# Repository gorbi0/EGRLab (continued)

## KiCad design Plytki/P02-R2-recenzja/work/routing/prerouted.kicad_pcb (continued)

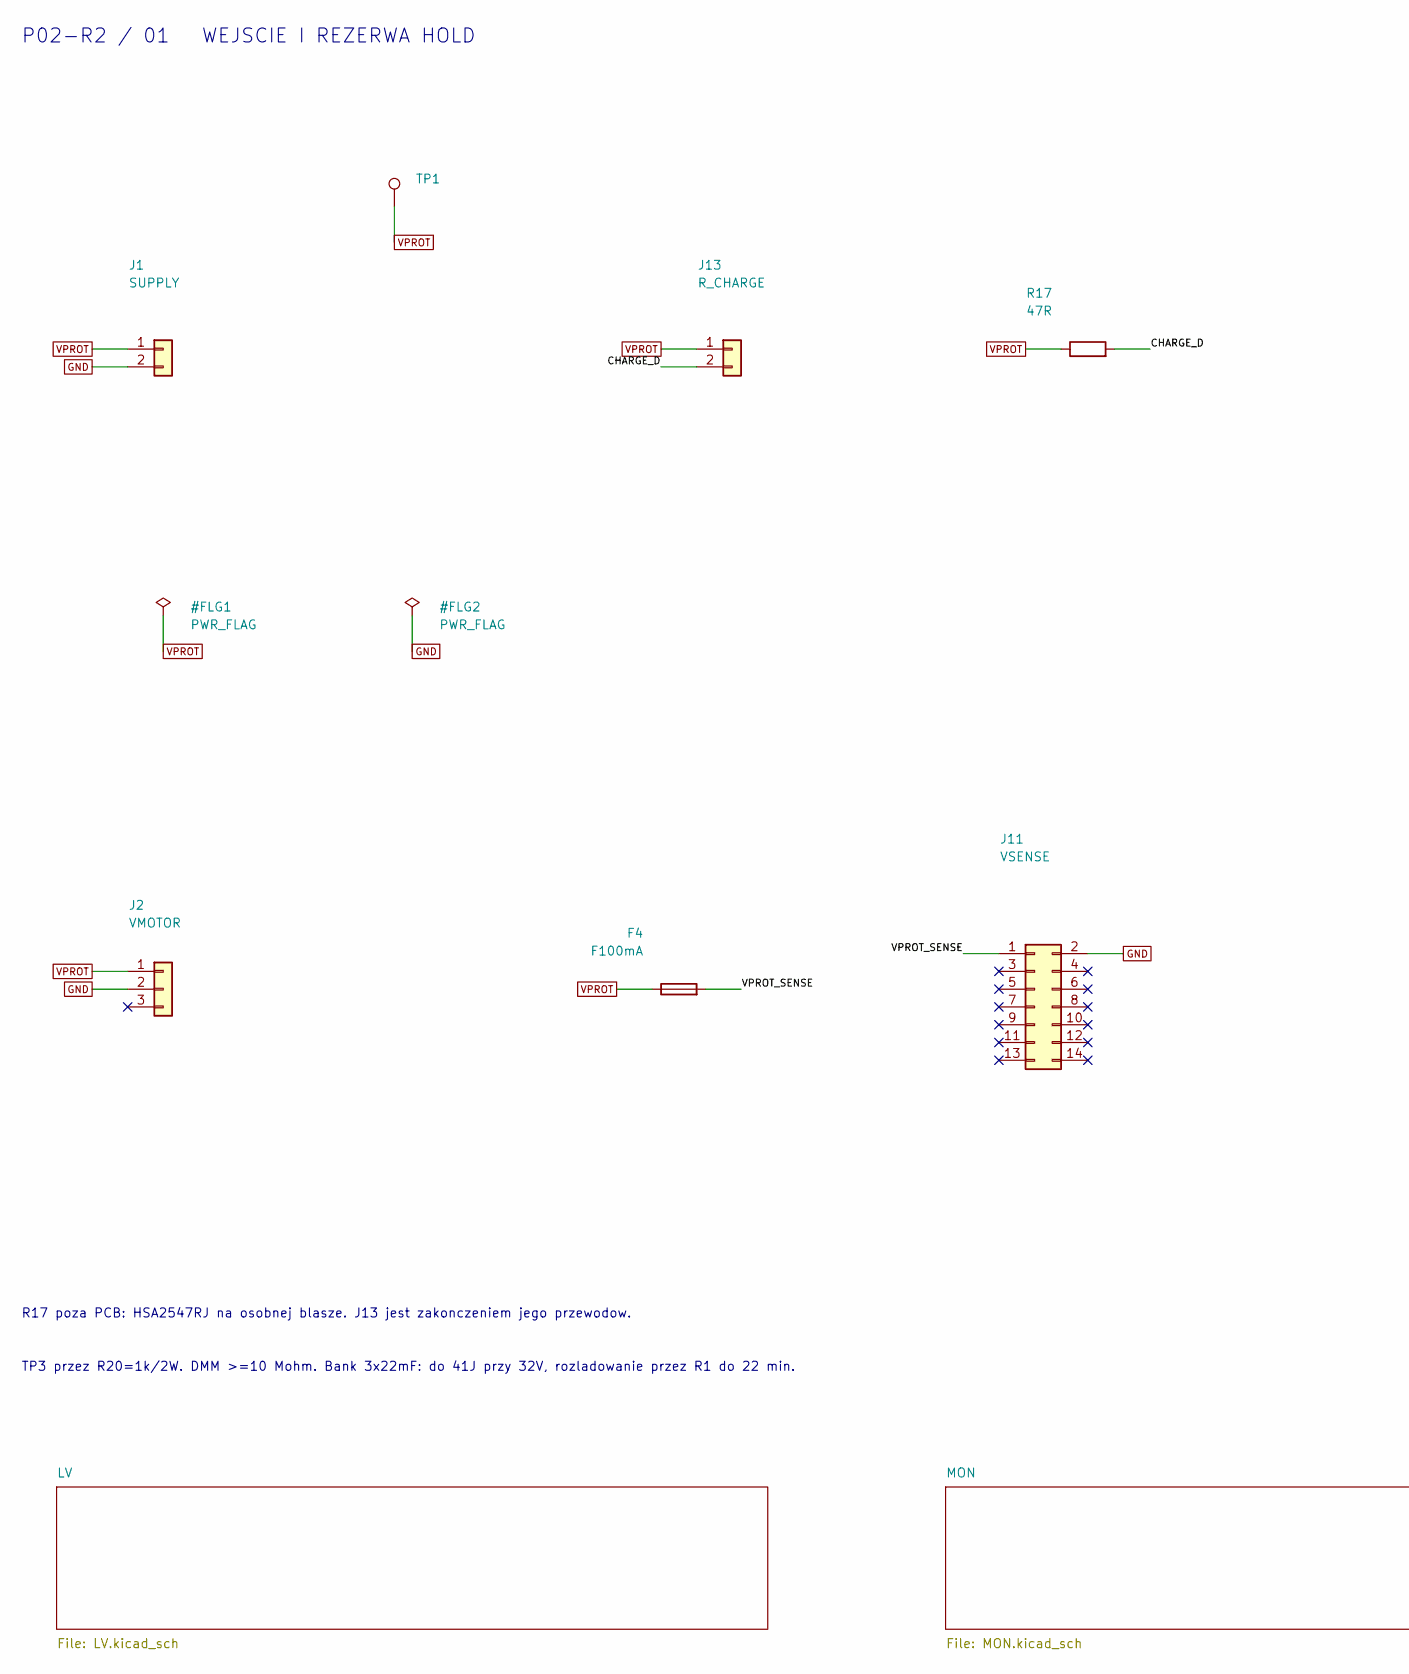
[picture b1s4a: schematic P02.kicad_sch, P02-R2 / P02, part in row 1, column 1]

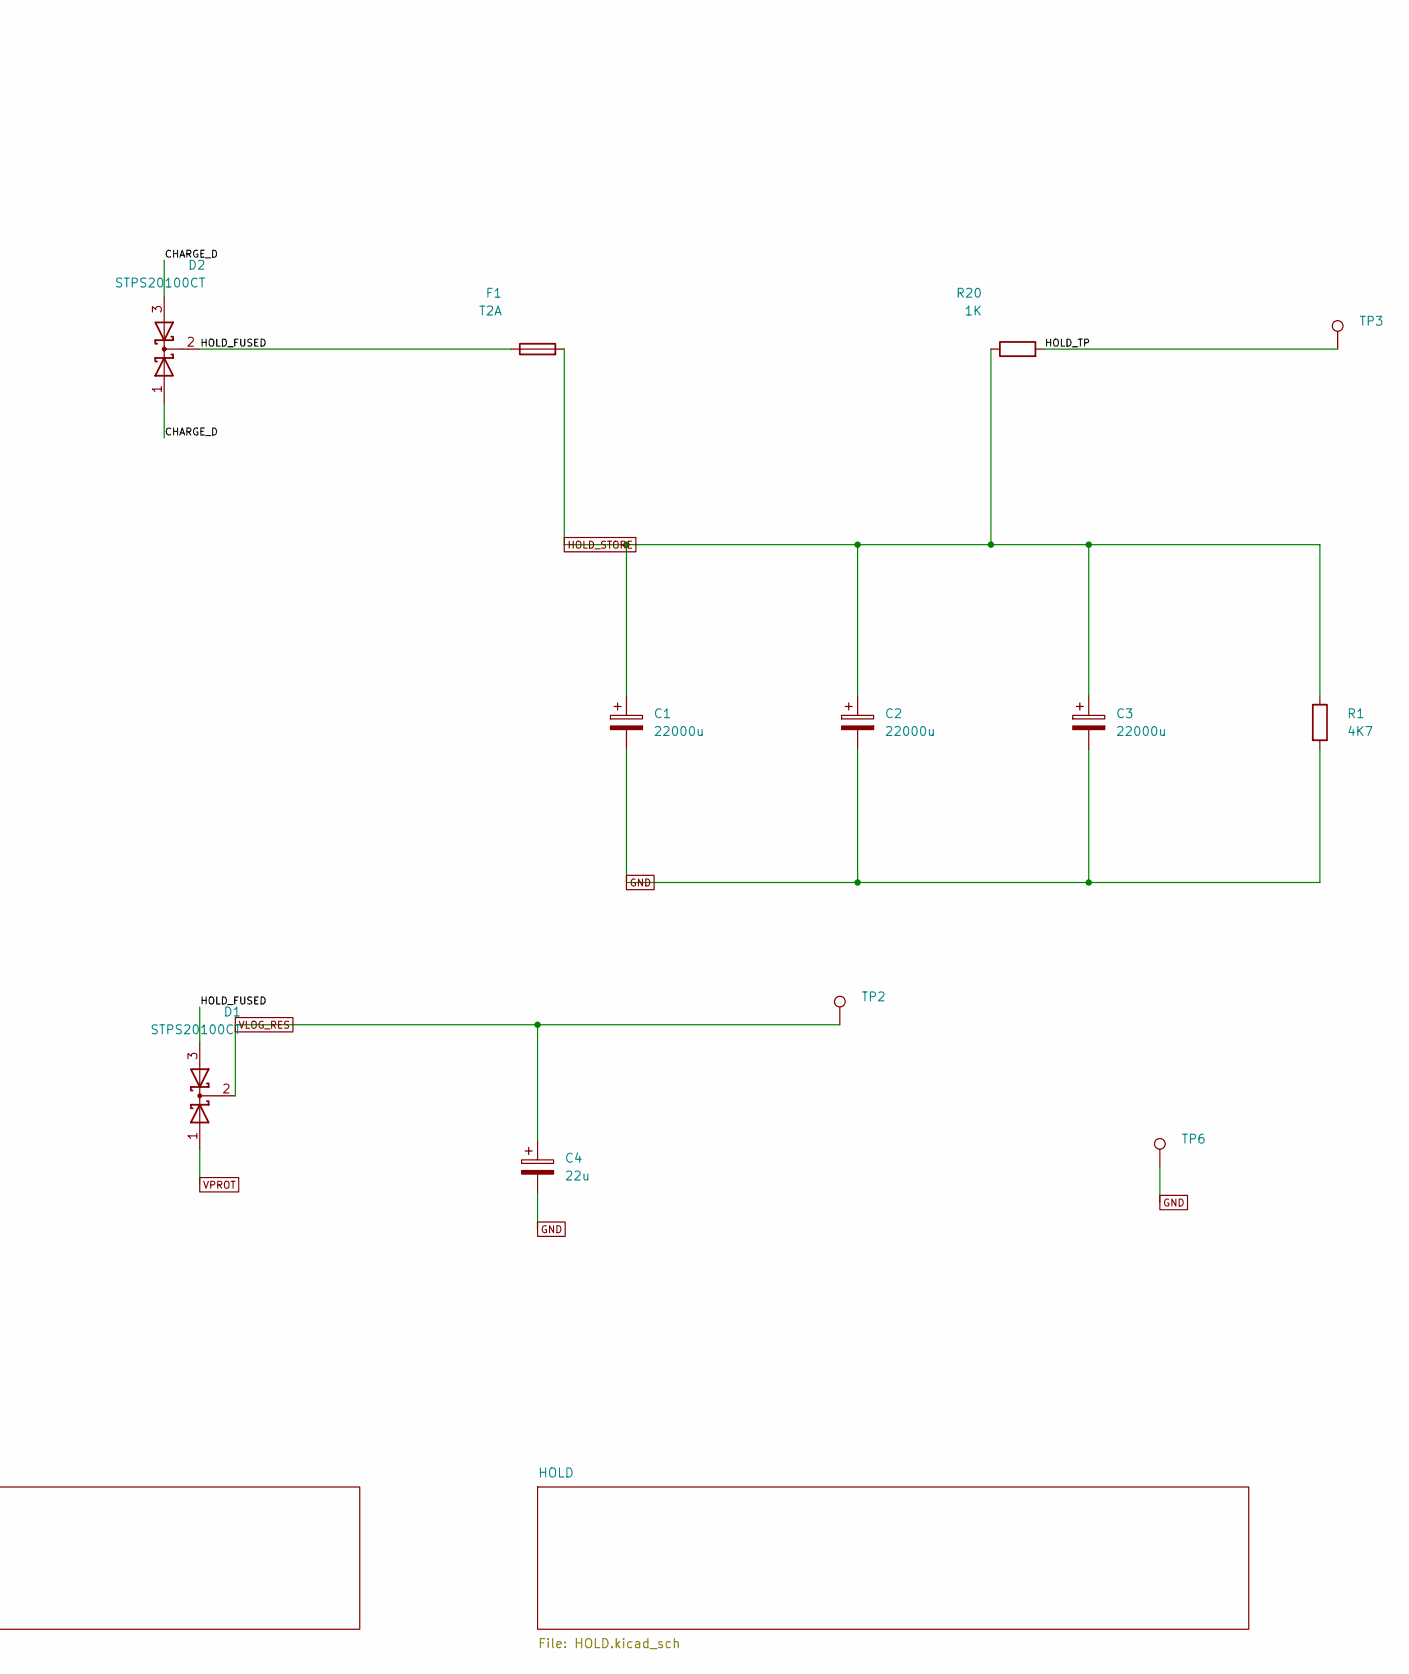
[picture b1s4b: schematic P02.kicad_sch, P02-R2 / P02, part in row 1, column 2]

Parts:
C1, C2, C3: 22000u; CP_Radial_D35.0mm_P10.00mm_SnapIn; MPN HC1V229M35045HA
C4: 22u; CP_Radial_D5.0mm_P2.00mm; MPN EEUFR1H220
D1, D2: STPS20100CT; TO220_3_P2.54_Drill1.4; MPN STPS20100CT
F1: T2A; Fuseholder_Cylinder-5x20mm_Stelvio-Kontek_PTF78_Horizontal_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; MPN Schurter 0001.2507 (T2A) + PTF78 holder
F4: F100mA; Fuseholder_Cylinder-5x20mm_Stelvio-Kontek_PTF78_Horizontal_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; MPN Stelvio-Kontek PTF78 + fuse F100mA >=32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
J1: SUPPLY; Pigtail_PWR_2x2.5mm2; MPN PCB termination; H_SUPPLY
J2: VMOTOR; PhoenixContact_GMSTBA_2,5_3-G-7,62_1x03_P7.62mm_Horizontal; MPN Phoenix GMSTBA 2,5/3-G-7,62 (1766246)
J11: VSENSE; Molex_Mini-Fit_Jr_5566-14A_2x07_P4.20mm_Vertical; MPN Molex 39-29-6148 (Au, vertical, no snap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
J13: R_CHARGE; Pigtail_RCHARGE_2xAWG20; MPN PCB termination; wires to HSA2547RJ
R1: 4K7; R_Axial_DIN0207_L6.3mm_D2.5mm_P10.16mm_Horizontal; MPN MF0207FTE-4K7
R17: 47R; MPN HSA2547RJ (TE 5-1625971-1)
R20: 1K; R_PR02_P17.78; MPN PR02000201001JA100
TP1, TP2, TP3, TP6: TestPad_1; MPN PCB test pad

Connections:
/CHARGE_D: D2.1 (A), D2.3 (A), J13.2, R17.2
/HOLD_FUSED: D1.3 (A), D2.2 (K), F1.1
/HOLD_TP: R20.2, TP3.1
/VPROT_SENSE: F4.2, J11.1
GND: C1.2, C2.2, C3.2, C4.2, J1.2, J2.2, J11.2, R1.2, TP6.1; also elsewhere on the board
HOLD_STORE: C1.1, C2.1, C3.1, F1.2, R1.1, R20.1; also elsewhere on the board
VLOG_RES: C4.1, D1.2 (K), TP2.1; also elsewhere on the board
VPROT: D1.1 (A), F4.1, J1.1, J2.1, J13.1, R17.1, TP1.1; also elsewhere on the board

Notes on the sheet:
P02-R2 / 01 WEJSCIE I REZERWA HOLD
R17 poza PCB: HSA2547RJ na osobnej blasze. J13 jest zakonczeniem jego przewodow.
TP3 przez R20=1k/2W. DMM >=10 Mohm. Bank 3x22mF: do 41J przy 32V, rozladowanie przez R1 do 22 min.

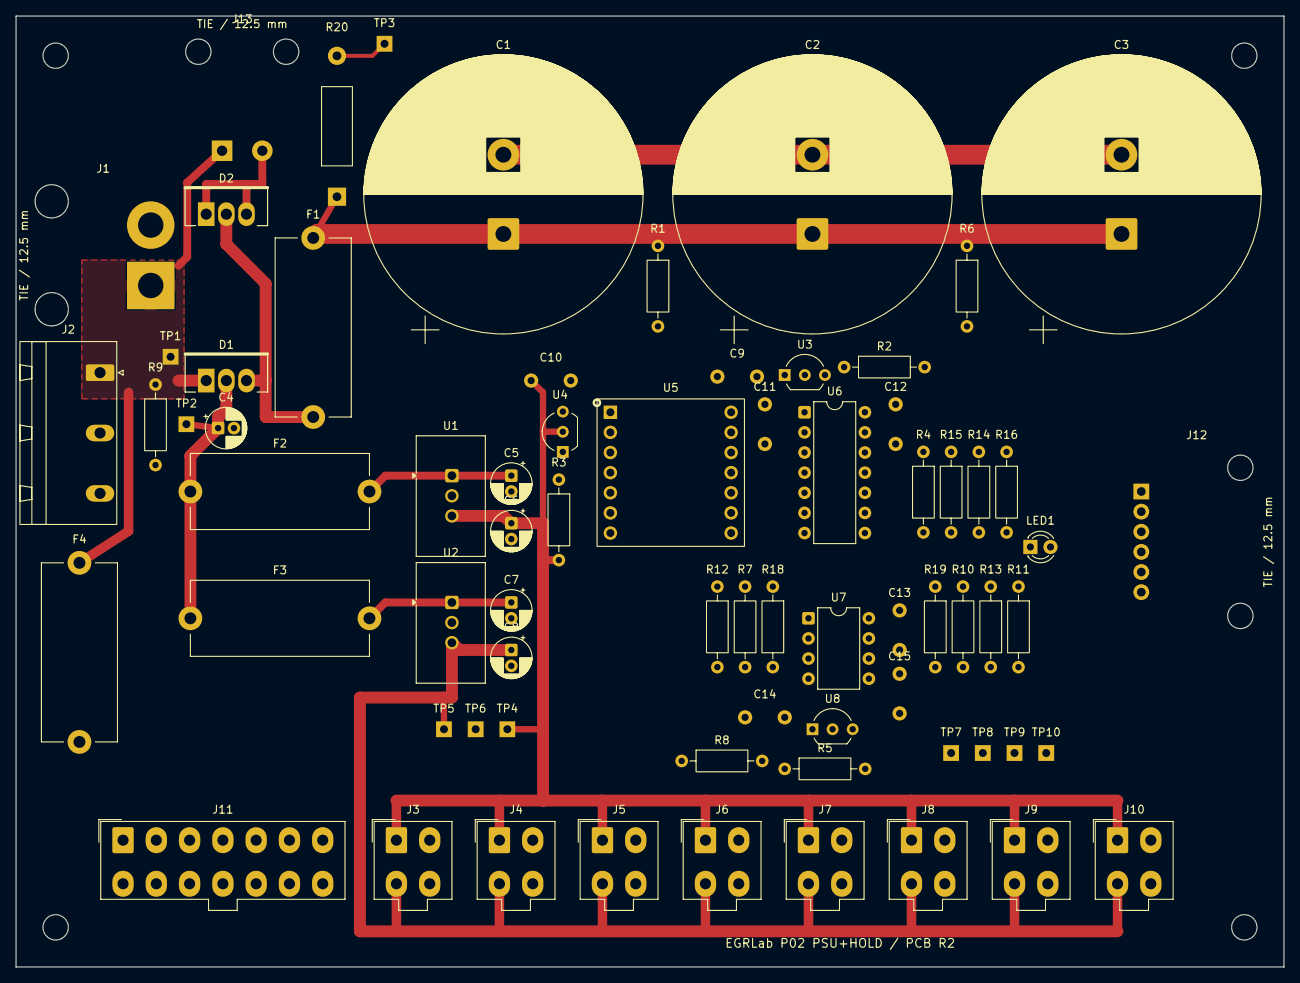
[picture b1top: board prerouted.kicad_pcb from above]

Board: 2 copper layers, 160.0 x 120.0 mm, 76 parts (0 on the bottom side), 27 nets.

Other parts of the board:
H1, H2, H3, H4: M3 NPTH
